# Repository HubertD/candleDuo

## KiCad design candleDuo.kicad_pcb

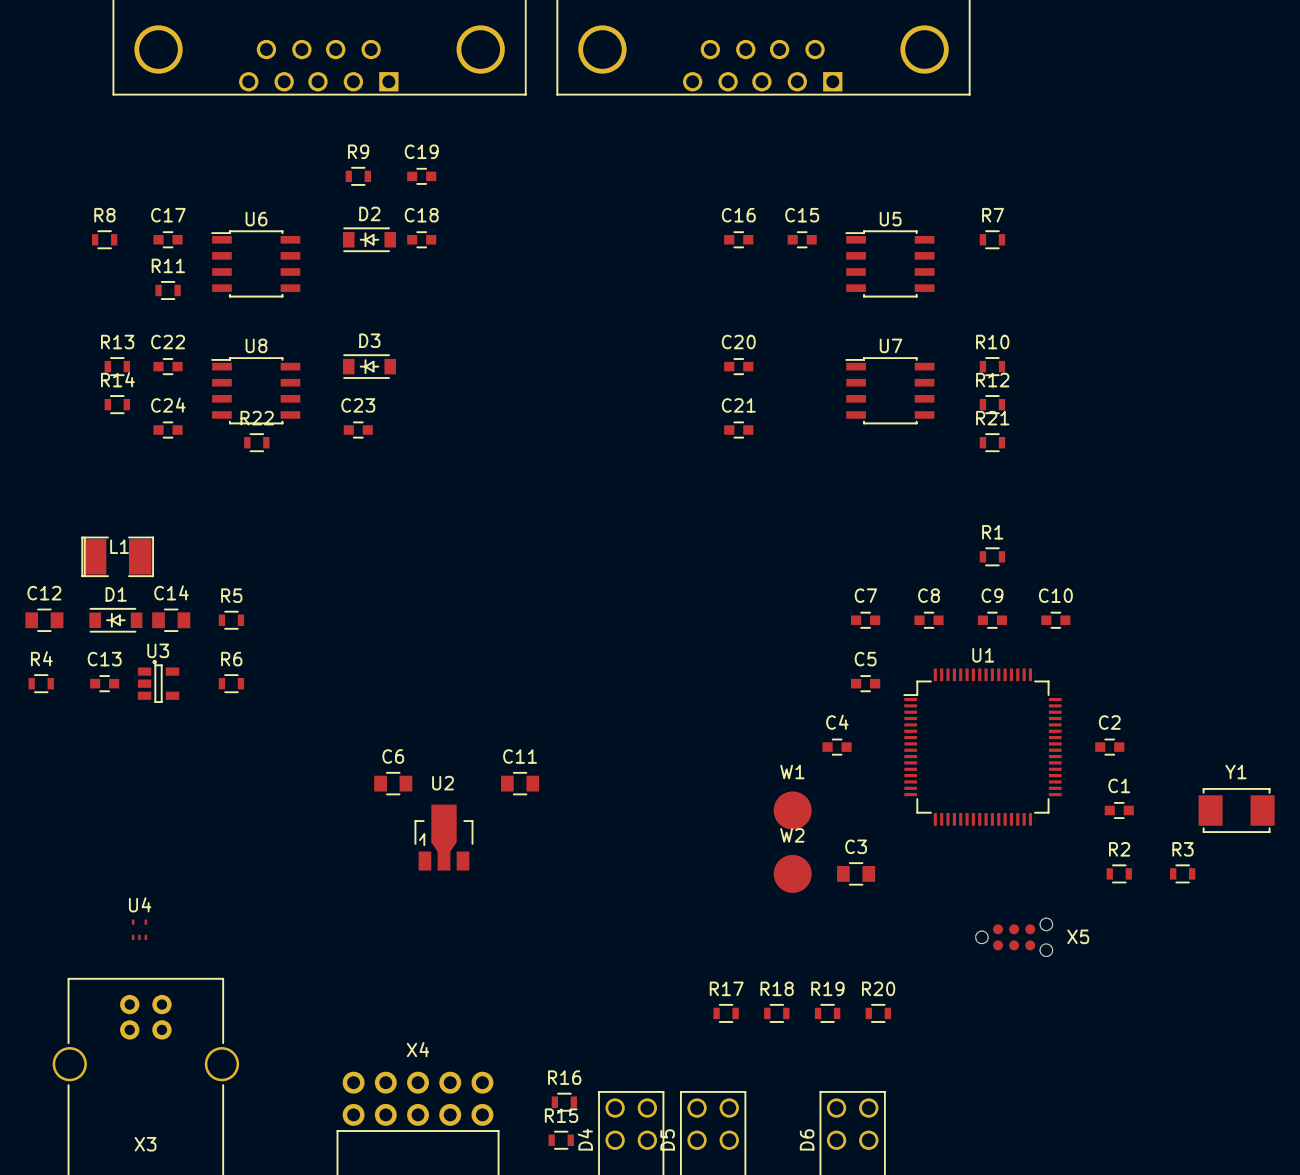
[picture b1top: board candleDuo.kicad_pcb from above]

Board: 2 copper layers, 69 parts (0 on the bottom side), 54 nets, no tracks yet.

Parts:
C1, C2: 18pF; C_0603
C3, C6, C11, C12, C14: 10uF; C_0805
C4, C5, C7, C8, C9, C10, C15, C16, C17, C20, C21, C22: 100nF; C_0603
C13, C18, C23: 220pF; C_0603
C19, C24: 1nF; C_0603
D1, D2, D3: MBR0520; SOD-123
D4, D5, D6: Led_Duo; dialight-553-07xxx
L1: 10uH/360mOhm; SMD-1210_Pol
R1, R8, R9, R13, R14, R15, R16, R17, R18, R19, R20: 1K; R_0603
R2, R3: 0R; R_0603
R4, R7, R11, R12, R22: 10K; R_0603
R5: 13.3K; R_0603
R6: 118K; R_0603
R10, R21: 120R; R_0603
U1: STM32F105RB; LQFP-64_10x10mm_Pitch0.5mm
U2: MCP1754ST-3302E/MB; SOT89-3_Housing
U3: LM27313; SOT-23-5
U4: TPD2E2U06; DRL_R-PDSO-N5
U5, U7: TJA1051/3; SOIC-8_3.9x4.9mm_Pitch1.27mm
U6, U8: TJA1021; SOIC-8_3.9x4.9mm_Pitch1.27mm
W1: UART_TX; Measurement_Point_Round-SMD-Pad_Big
W2: UART_RX; Measurement_Point_Round-SMD-Pad_Big
X1, X2: DB9; DB9MC
X3: USB_B
X4: APEM_DA05; APEM_DA_05
X5: CON_SWD; TC2030-NL
Y1: 8 MHz; ABM3

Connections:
+3V3: C3.1, C5.1, C7.1, C8.1, C9.1, C10.1, C11.1, C16.1, C21.1, R7.1, R8.2, R11.2, R12.1, R13.2, R15.1, R16.1, R17.1, R18.1, R19.1, R20.1, R22.2, U1.1, U1.13, U1.19, U1.32, U1.48, U1.64, U2.3, U5.5, U7.5, X4.2, X5.1
+5V: C6.1, C12.1, C15.1, C20.1, L1.1, R4.1, U2.2, U3.5, U5.3, U7.3, X3.1
+12V: C13.1, C14.1, C17.1, C22.1, D1.1, D2.2, D3.2, R6.1, U6.7, U8.7
CAN1_H: R10.2, U5.7, X1.7
CAN1_L: U5.6, X1.2, X4.3
CAN1_RX: U1.61, U5.4
CAN1_S: R7.2, U1.59, U5.8
CAN1_TX: U1.62, U5.1
CAN2_H: R21.1, U7.7, X2.7
CAN2_L: U7.6, X2.2, X4.7
CAN2_RX: U1.57, U7.4
CAN2_S: R12.2, U1.56, U7.8
CAN2_TX: U1.58, U7.1
GND: C1.2, C2.2, C3.2, C4.2, C5.2, C6.2, C7.2, C8.2, C9.2, C10.2, C11.2, C12.2, C14.2, C15.2, C16.2, C17.2, C18.2, C19.2, C20.2, C21.2, C22.2, C23.2, C24.2, D6.4, R1.2, R5.1, U1.12, U1.18, U1.31, U1.47, U1.63, U2.1, U3.2, U4.4, U5.2, U6.5, U7.2, U8.5, X1.3, X2.3, X3.4, X3.5, X5.3
LED0: D4.2, U1.20
LED1: D4.4, U1.21
LED2: D5.2, U1.22
LED3: D5.4, U1.23
LED4: D6.2, U1.41
LIN1: C18.1, U6.6, X1.4, X4.5
LIN1_RX: R8.1, U1.43, U6.1
LIN1_TX: U1.42, U6.4
LIN2: C23.1, U8.6, X2.4, X4.9
LIN2_RX: R13.1, U8.1
NRST: C4.1, U1.7, X5.5
unnamed: C1.1, R2.2, Y1.2
unnamed: C2.1, R3.2, Y1.1
unnamed: C13.2, R5.2, R6.2, U3.3
unnamed: C19.1, R9.1, X4.6
unnamed: C24.1, R14.1, X4.10
unnamed: D1.2, L1.2, U3.1
unnamed: D2.1, R9.2
unnamed: D3.1, R14.2
unnamed: D4.1, R15.2
unnamed: D4.3, R16.2
unnamed: D5.1, R17.2
unnamed: D5.3, R18.2
unnamed: D6.1, R19.2
unnamed: D6.3, R20.2
unnamed: R1.1, U1.60, X4.1
unnamed: R2.1, U1.5
unnamed: R3.1, U1.6
unnamed: R4.2, U3.4
unnamed: R10.1, X4.4
unnamed: R11.1, U6.2
unnamed: R21.2, X4.8
unnamed: R22.1, U8.2
unnamed: U1.16, W1.1
unnamed: U1.17, W2.1
SWCLK: U1.49, X5.2
SWDIO: U1.46, X5.4
SWO: U1.55, X5.6
USB_DM: U4.3, X3.2
USB_DP: U4.5, X3.3

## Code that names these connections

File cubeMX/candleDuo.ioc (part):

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Mcu.Name=STM32F105R(8-B-C)Tx
Mcu.Package=LQFP64
Mcu.UserName=STM32F105RBTx
PA10.Mode=LIN
PA10.Signal=USART1_RX
PA11.Mode=Device_Only
PA11.Signal=USB_OTG_FS_DM
PA12.Mode=Device_Only
PA12.Signal=USB_OTG_FS_DP
PA13.Mode=Trace_Asynchronous_SW
PA13.Signal=SYS_JTMS-SWDIO
PA14.Mode=Trace_Asynchronous_SW
PA14.Signal=SYS_JTCK-SWCLK
PA2.Mode=Asynchronous
PA2.Signal=USART2_TX
PA3.Mode=Asynchronous
PA3.Signal=USART2_RX
PA4.GPIOParameters=GPIO_Label
PA4.GPIO_Label=LED0
PA4.Signal=GPIO_Output
PA5.GPIOParameters=GPIO_Label
PA5.GPIO_Label=LED1
PA5.Signal=GPIO_Output
PA6.GPIOParameters=GPIO_Label
PA6.GPIO_Label=LED2
PA6.Signal=GPIO_Output
PA7.GPIOParameters=GPIO_Label
PA7.GPIO_Label=LED3
PA7.Signal=GPIO_Output
PA8.GPIOParameters=GPIO_Label
PA8.GPIO_Label=LED4
PA8.Signal=GPIO_Output
PA9.Mode=LIN
PA9.Signal=USART1_TX
PB3.Mode=Trace_Asynchronous_SW
PB3.Signal=SYS_TRACESWO
PB4.GPIOParameters=GPIO_Label
PB4.GPIO_Label=CAN2_S
PB4.Signal=GPIO_Output
PB5.Mode=Slave
PB5.Signal=CAN2_RX
PB6.Mode=Slave
PB6.Signal=CAN2_TX
PB7.GPIOParameters=GPIO_Label
PB7.GPIO_Label=CAN1_S
PB7.Signal=GPIO_Output
PB8.Mode=Master
PB8.Signal=CAN1_RX
PB9.Mode=Master
PB9.Signal=CAN1_TX
PC10.Mode=LIN
PC10.Signal=USART3_TX
PC11.Mode=LIN
PC11.Signal=USART3_RX
PD0-OSC_IN.Mode=HSE-External-Oscillator
PD0-OSC_IN.Signal=RCC_OSC_IN
PD1-OSC_OUT.Mode=HSE-External-Oscillator
PD1-OSC_OUT.Signal=RCC_OSC_OUT
RCC.SYSCLKFreq_VALUE=48000000
RCC.SYSCLKSource=RCC_SYSCLKSOURCE_PLLCLK

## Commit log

2016-05-23 initial checkin
2016-05-23 swap LEDs
2016-05-23 drive LEDs with +3V3
2016-05-23 use duo leds
2016-05-23 assign most footprints
2016-05-23 assign all footprints
2016-05-24 some routing
